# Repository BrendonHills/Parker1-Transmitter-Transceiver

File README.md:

# The Parker1-Transmitter / Transceiver
The design of a ten band HF transmitter / transceiver and winner of the G-QRP Club Memorial Trophy 2024.

Please see the attached submission to the G-QRP Club for a full description of the project. Circuit diagrams and PCB files are in Ki-Cad 7.0
software and you may need to download that in order to view.

The transmitter consists of two parts, the Nano VFO and the HF Multi-band PA, connected together to make the transmitter. 
Note that the HF PA board is designed to have the QRPLabs LPF Relay board mounted on it to provide five LPFs covering ten bands (160-10m.)

Since this submission, the transmitter is now a transceiver, with the addition of a QRPLabs RX module, 
Hi-Per-Mite CW filter and audio amp. This is not protrayed in the diagrams here, but the circuit diagrams of the TX and VFO should make connections clear.
The L-Match ATU and internal battery pack are also not depicted, and there are no diagrams for this, but you should be able to work this out yourself.
All that is shown here is the code, circuit diagrams and PCB files for the VFO and for the PA board, nothing else,
however it is a great place to start and then experiment further.

I AM SORRY BUT I AM TOO BUSY TO OFFER SUPPORT OR ANSWER QUESTIONS (I have already answered a lot!) Please do not attempt this project without being
aware of that and reasonably confident in your abilities. My advice would to be just build the VFO first. The provided transceiver code will still work with just the VFO, but be aware that the code only activates the Si5351 clocks for TX and TX when those modes are in operation. In other words, to use just the VFO you would need to modify the clock output code to acheive a permanent clock / VFO output if that is what is required.

You will need to modify the code yourself to select your starting frequency and your callsign / CQ message. I have tried to make the code clear with plenty of remarks.
You will also need to amend the code to choose the RX frequency settings (i.e. offset, etc.) These options are NOT menu driven and must be done within the code
before uploading to the VFO. Therefore a degree of construction and programming experience is absolutely required.

The project has attracted quite a bit of interest since recently winning the G-QRP Club 2024 Construction Competition (G3RJV Trophy) and the intent
of this repository is to assist those interested in building it or using it as a platform for their own projects. I am sorry I am unable to help further but
hope this is of use.

Good luck.
Daimon, G4USI.

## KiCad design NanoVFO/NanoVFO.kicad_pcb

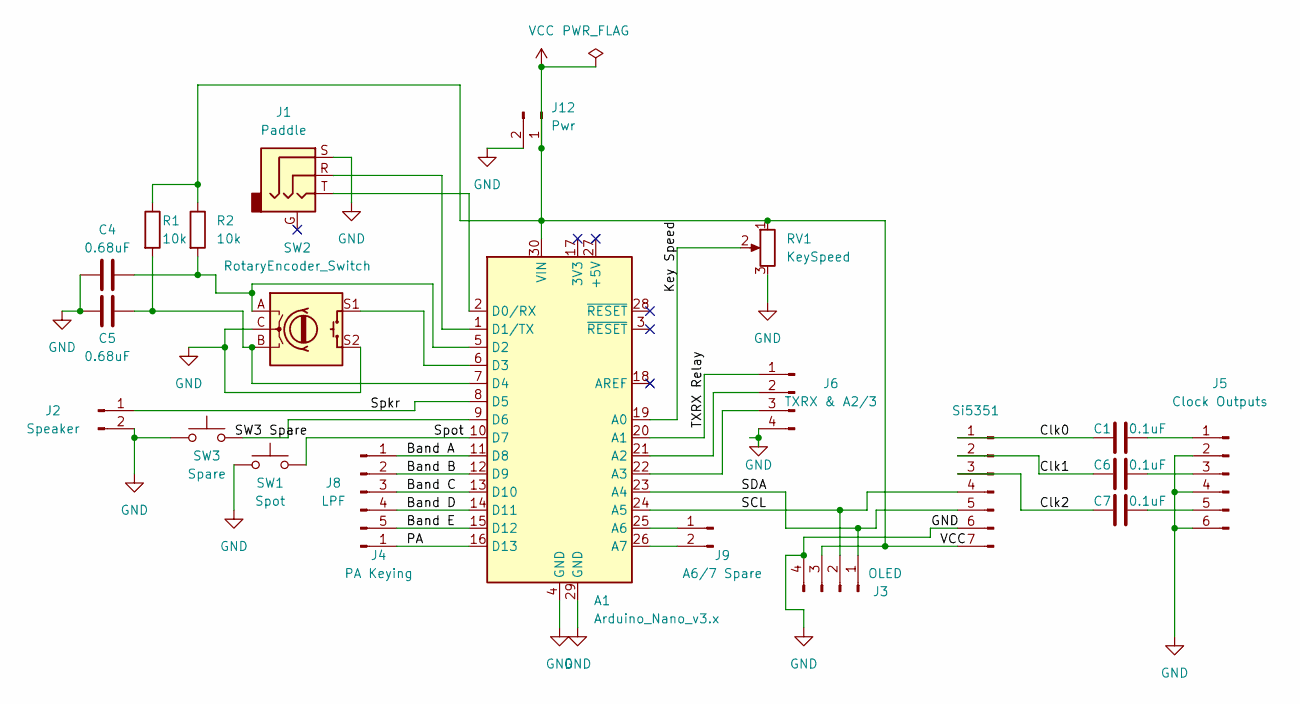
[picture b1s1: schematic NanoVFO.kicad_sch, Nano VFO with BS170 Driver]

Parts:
A1: Arduino_Nano_v3.x; Arduino_Nano
C1, C6, C7: 0.1uF; C_Disc_D4.7mm_W2.5mm_P5.00mm
C4, C5: 0.68uF; C_Disc_D4.7mm_W2.5mm_P5.00mm
J1: Paddle; Jack_3.5mm_QingPu_WQP-PJ366ST_Vertical
J2: Speaker; PinHeader_1x02_P2.54mm_Vertical
J3: OLED; Display_128x64_096_I2C
J4: PA Keying; PinHeader_1x01_P2.54mm_Vertical
J5: Clock Outputs; PinHeader_1x06_P2.54mm_Vertical
J6: TXRX & A2/3; PinHeader_1x04_P2.54mm_Vertical
J8: LPF; PinHeader_1x05_P2.54mm_Vertical
J9: A6/7 Spare; PinHeader_1x02_P2.54mm_Vertical
J10: Si5351; Si5351 Vertical
J12: Pwr; PinHeader_1x02_P2.54mm_Vertical
R1, R2: 10k; R_Axial_DIN0207_L6.3mm_D2.5mm_P7.62mm_Horizontal
RV1: KeySpeed; Potentiometer_Alpha_RD901F-40-00D_Single_Vertical
SW1: Spot; Push_E-Switch_KS01Q01
SW2: RotaryEncoder_Switch; RotaryEncoder_Alps_EC11E-Switch_Vertical_H20mm
SW3: Spare; Push_E-Switch_KS01Q01

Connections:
/Band A: A1.11 (D8), J8.1
/Band B: A1.12 (D9), J8.2
/Band C: A1.13 (D10), J8.3
/Band D: A1.14 (D11), J8.4
/Band E: A1.15 (D12), J8.5
/Clk0: C1.2, J10.1
/Clk1: C6.1, J10.2
/Clk2: C7.1, J10.3
/Key Speed: A1.19 (A0), RV1.2
/PA: A1.16 (D13), J4.1
/SCL: A1.24 (A5), J3.2, J10.4
/SDA: A1.23 (A4), J3.1, J10.5
/Spkr: A1.8 (D5), J2.1
/Spot: A1.10 (D7), SW1.2
/TXRX Relay: A1.20 (A1), J6.1
GND: A1.4 (GND), A1.29 (GND), C4.2, C5.2, J1.S, J2.2, J3.4, J5.2, J5.4, J5.6, J6.4, J10.6, J12.2, RV1.3, SW1.1, SW2.C, SW2.S2, SW3.1
unnamed: A1.21 (A2), J6.2
unnamed: A1.22 (A3), J6.3
unnamed: A1.25 (A6), J9.1
unnamed: A1.26 (A7), J9.2
unnamed: A1.2 (D0/RX), J1.T
unnamed: A1.1 (D1/TX), J1.R
unnamed: A1.5 (D2), C4.1, R2.2, SW2.A
unnamed: A1.6 (D3), SW2.S1
unnamed: A1.7 (D4), C5.1, R1.2, SW2.B
unnamed: A1.9 (D6), SW3.2
unnamed: C1.1, J5.1
unnamed: C6.2, J5.3
unnamed: C7.2, J5.5
VCC: A1.30 (VIN), J3.3, J10.7, J12.1, R1.1, R2.1, RV1.1

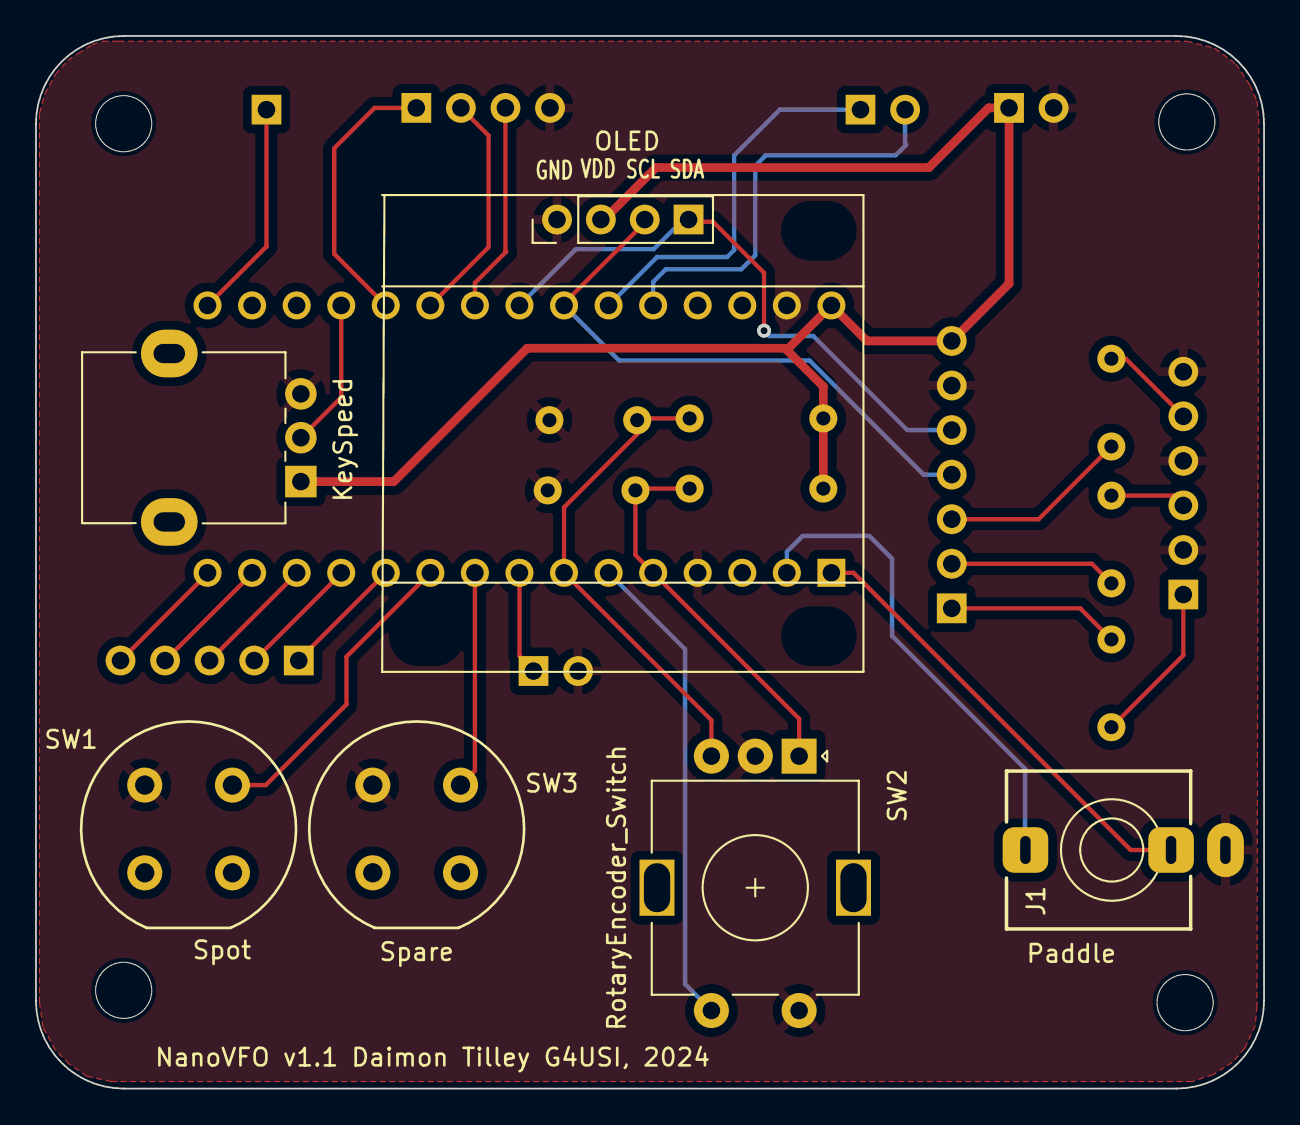
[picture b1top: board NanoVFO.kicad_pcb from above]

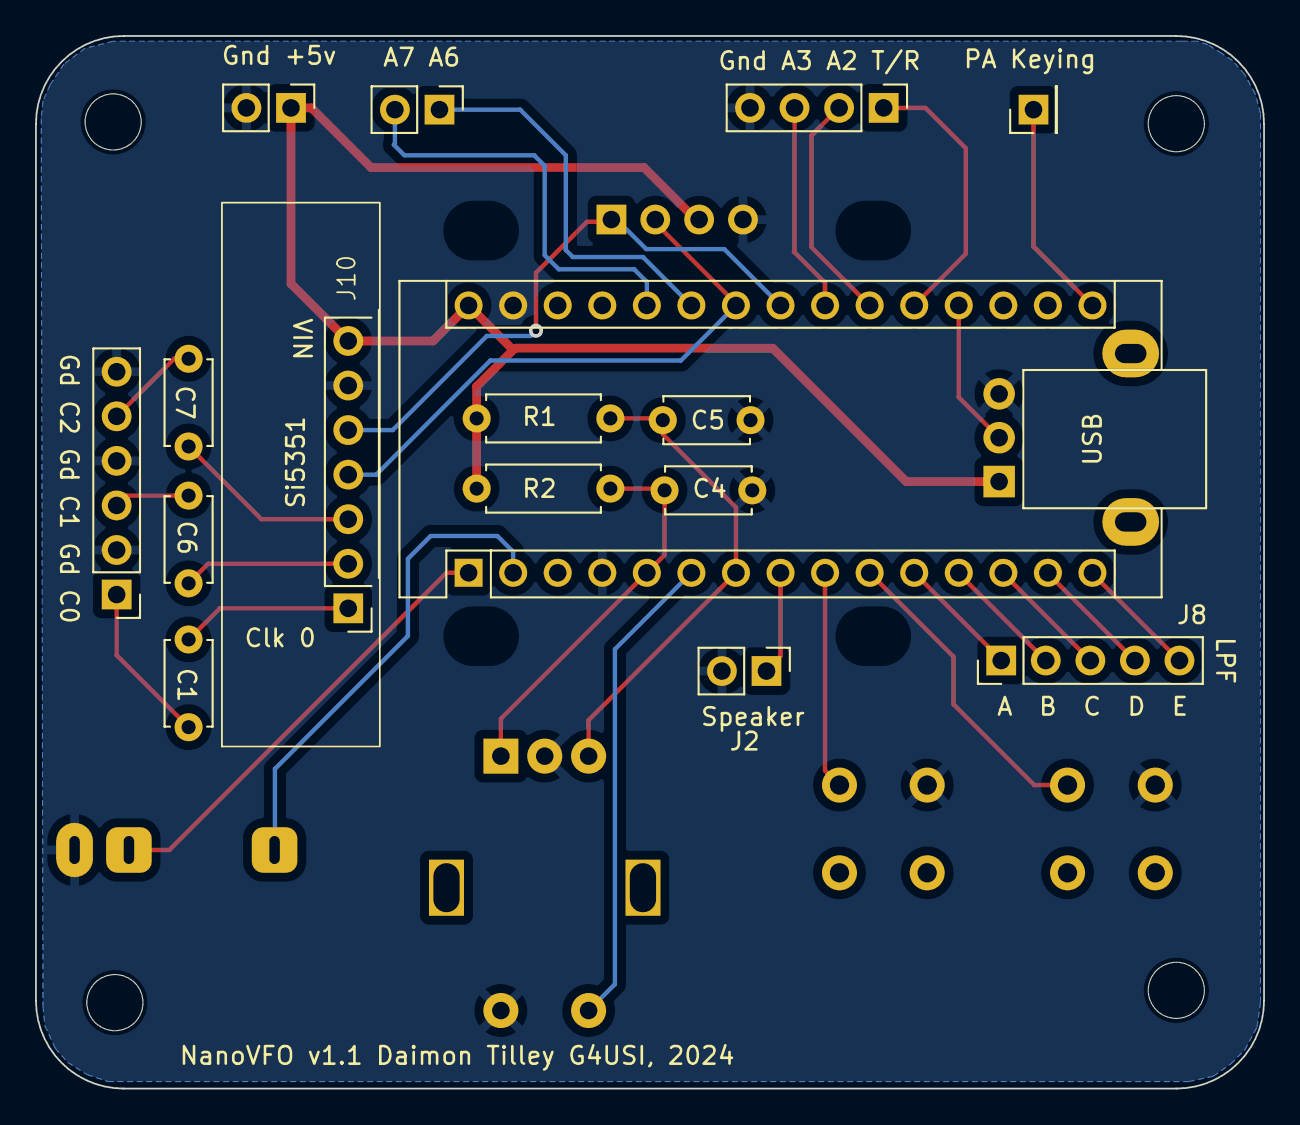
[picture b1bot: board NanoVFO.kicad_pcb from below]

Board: 2 copper layers, 70.0 x 60.0 mm, 22 parts (16 on the bottom side), 30 nets.

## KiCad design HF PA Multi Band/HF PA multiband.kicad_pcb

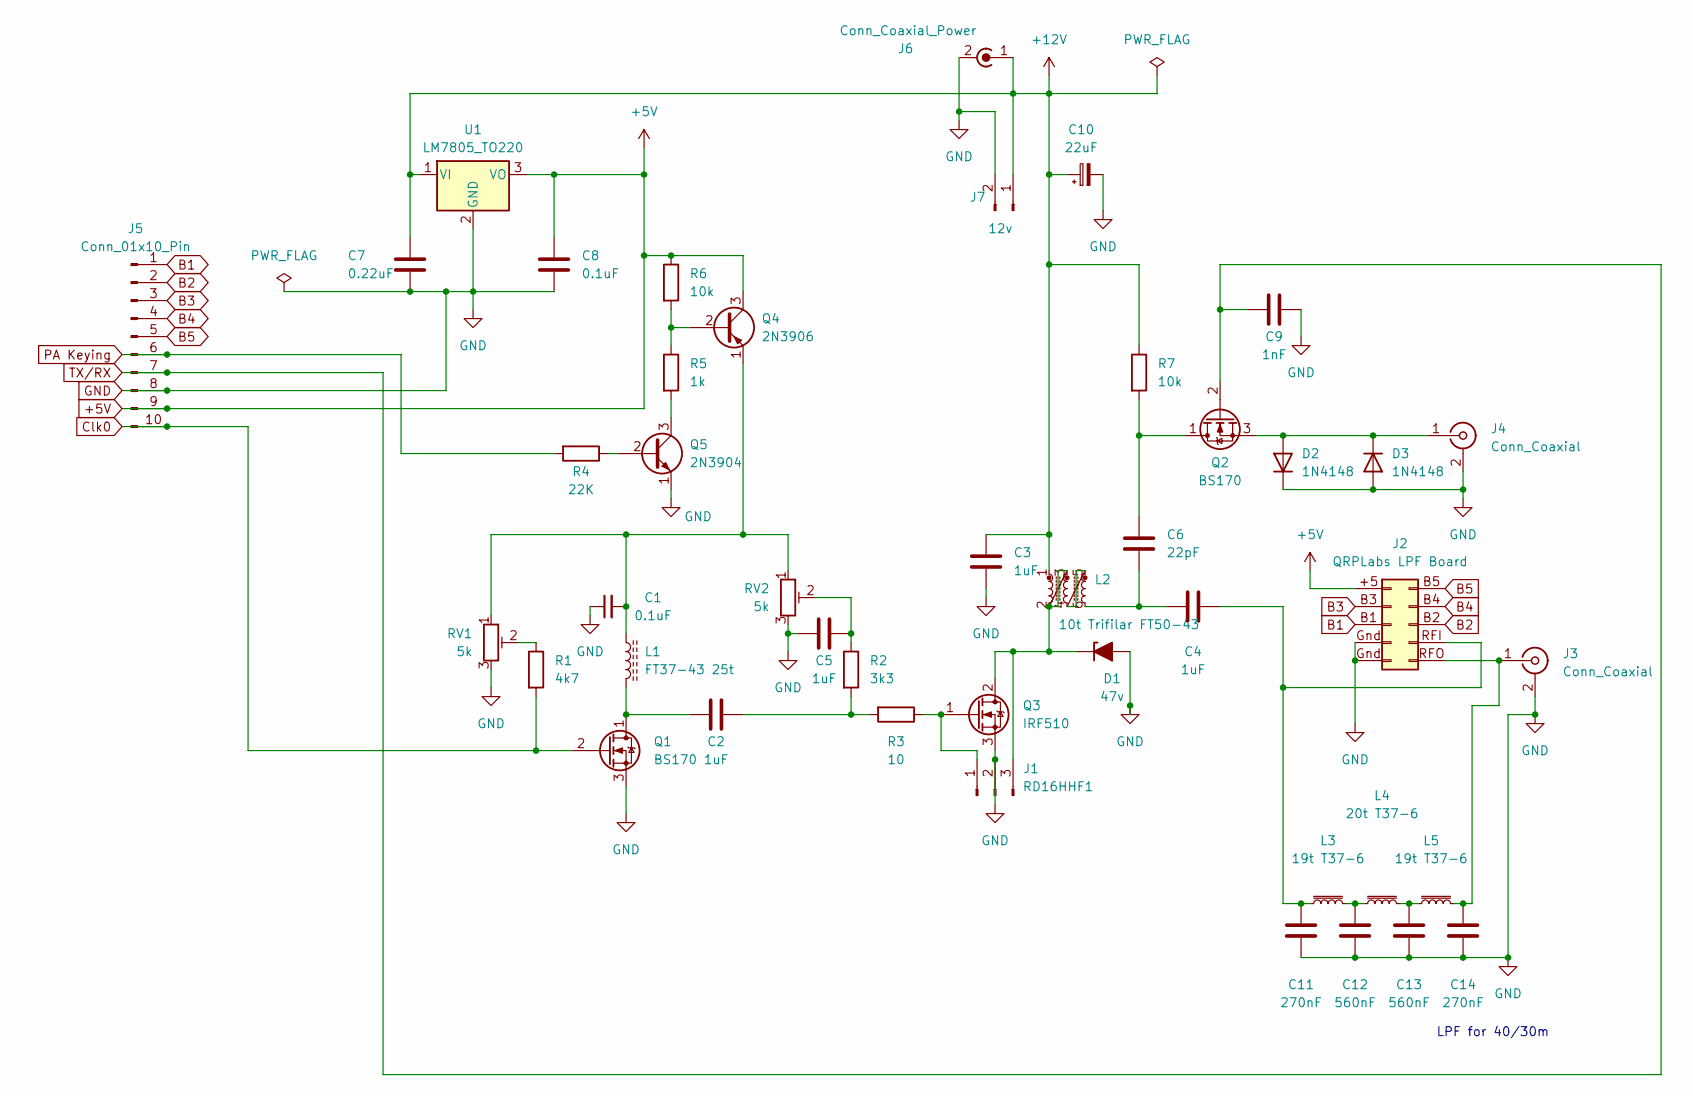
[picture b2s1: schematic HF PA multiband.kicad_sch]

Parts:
C1, C8: 0.1uF; C_Disc_D4.7mm_W2.5mm_P5.00mm
C2, C3, C4, C5: 1uF; C_Disc_D4.7mm_W2.5mm_P5.00mm
C6: 22pF; C_Disc_D4.7mm_W2.5mm_P5.00mm
C7: 0.22uF; C_Disc_D4.7mm_W2.5mm_P5.00mm
C9: 1nF; C_Disc_D4.7mm_W2.5mm_P5.00mm
C10: 22uF; CP_Radial_D5.0mm_P2.00mm
C11, C14: 270nF; C_Disc_D4.7mm_W2.5mm_P5.00mm
C12, C13: 560nF; C_Disc_D4.7mm_W2.5mm_P5.00mm
D1: 47v; D_DO-34_SOD68_P7.62mm_Horizontal
D2, D3: 1N4148; D_DO-35_SOD27_P7.62mm_Horizontal
J1: RD16HHF1; PinHeader_1x03_P2.54mm_Vertical
J2: QRPLabs LPF Board; QRPLabs LPF Relay Board
J3, J4: Conn_Coaxial; BNC_TEConnectivity_1478035_Horizontal
J5: Conn_01x10_Pin; PinHeader_1x10_P2.54mm_Vertical
J6: Conn_Coaxial_Power; BarrelJack_Wuerth_6941xx301002
J7: 12v; PinHeader_1x02_P2.54mm_Vertical
L1: FT37-43 25t; L_Toroid_Vertical_L10.0mm_W5.0mm_P5.08mm
L2: 10t Trifilar FT50-43; L_Trifilar_FT50_43
L3, L5: 19t T37-6; L_Toroid_Vertical_L10.0mm_W5.0mm_P5.08mm
L4: 20t T37-6; L_Toroid_Vertical_L10.0mm_W5.0mm_P5.08mm
Q1, Q2: BS170; TO-92_Inline
Q3: IRF510; TO-220-3_Vertical
Q4: 2N3906; TO-92_Inline
Q5: 2N3904; TO-92_Inline
R1: 4k7; R_Axial_DIN0207_L6.3mm_D2.5mm_P7.62mm_Horizontal
R2: 3k3; R_Axial_DIN0207_L6.3mm_D2.5mm_P7.62mm_Horizontal
R3: 10; R_Axial_DIN0207_L6.3mm_D2.5mm_P7.62mm_Horizontal
R4: 22K; R_Axial_DIN0207_L6.3mm_D2.5mm_P7.62mm_Horizontal
R5: 1k; R_Axial_DIN0207_L6.3mm_D2.5mm_P7.62mm_Horizontal
R6, R7: 10k; R_Axial_DIN0207_L6.3mm_D2.5mm_P7.62mm_Horizontal
RV1, RV2: 5k; Potentiometer_Bourns_3296W_Vertical
U1: LM7805_TO220; TO-220-3_Vertical

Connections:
+5V: C8.1, J2.+5 (Pin_1), J5.9, Q4.3 (C), R6.1, U1.3 (VO)
+12V: C3.1, C7.1, C10.1, J6.1 (In), J7.1, L2.1, R7.1, U1.1 (VI)
B1: J2.B1 (Pin_3), J5.1
B2: J2.B2 (Pin_8), J5.2
B3: J2.B3 (Pin_2), J5.3
B4: J2.B4 (Pin_9), J5.4
B5: J2.B5 (Pin_10), J5.5
Clk0: J5.10, Q1.2 (G), R1.2
GND: C1.1, C3.2, C5.2, C7.2, C8.2, C9.2, C10.2, C11.2, C12.2, C13.2, C14.2, D1.2 (A), D2.1 (K), D3.2 (A), J1.2, J2.Gnd (Pin_4), J3.2 (Ext), J4.2 (Ext), J5.8, J6.2 (Ext), J7.2, Q1.3 (S), Q3.3 (S), Q5.1 (E), RV1.3, RV2.3, U1.2 (GND)
unnamed: C2.1, R2.2, R3.2
unnamed: C4.2, C6.2, L2.6
unnamed: C5.1, R2.1, RV2.2
unnamed: C12.1, L3.2, L4.1
unnamed: C13.1, L4.2, L5.1
unnamed: D1.1 (K), J1.3, L2.2, L2.3, Q3.2 (D)
unnamed: D2.2 (A), D3.1 (K), J4.1 (In), Q2.3 (S)
unnamed: J1.1, Q3.1 (G), R3.1
unnamed: C14.1, J2.RFO (Pin_6), J3.1 (In), L5.2
unnamed: C4.1, C11.1, J2.RFI (Pin_7), L3.1
unnamed: L2.4, L2.5
unnamed: C2.2, L1.2, Q1.1 (D)
unnamed: C6.1, Q2.1 (D), R7.2
unnamed: Q4.2 (B), R5.1, R6.2
unnamed: C1.2, L1.1, Q4.1 (E), RV1.1, RV2.1
unnamed: Q5.2 (B), R4.1
unnamed: Q5.3 (C), R5.2
unnamed: R1.1, RV1.2
PA Keying: J5.6, R4.2
TX/RX: C9.1, J5.7, Q2.2 (G)

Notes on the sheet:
LPF for 40/30m

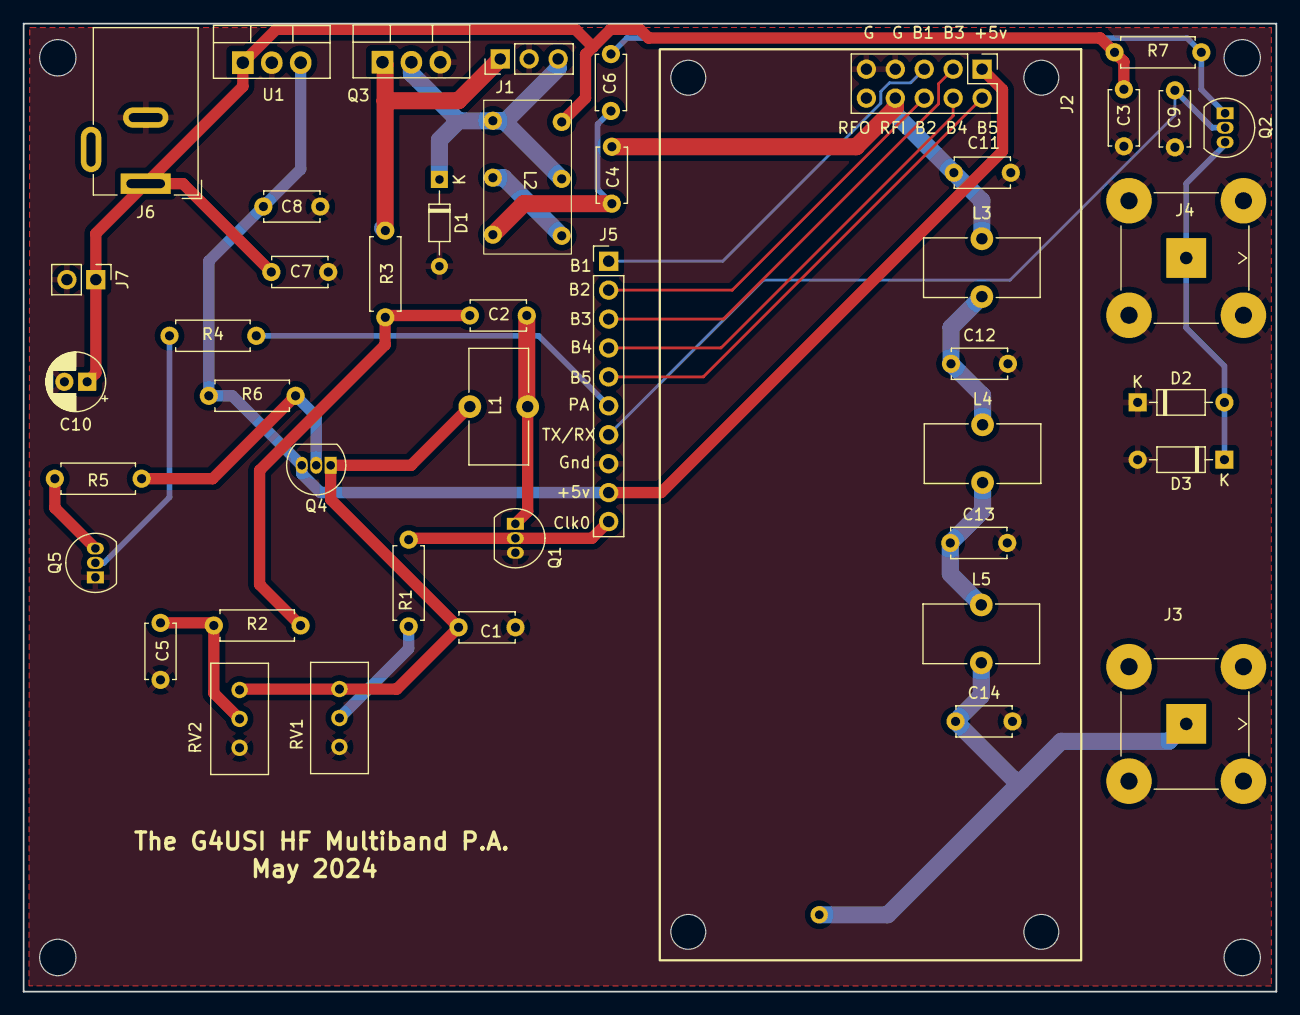
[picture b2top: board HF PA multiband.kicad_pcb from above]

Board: 2 copper layers, 110.0 x 85.0 mm, 44 parts (0 on the bottom side), 29 nets.

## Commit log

2025-03-31 README.md
